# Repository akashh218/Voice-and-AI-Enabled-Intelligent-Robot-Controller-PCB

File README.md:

# Voice and AI-Enabled Intelligent Robot Controller PCB

A custom **4-layer embedded robotics controller PCB** designed for a multifunctional voice-interactive robot. The board integrates motor control, servo control, voice recognition, AI audio interaction, environmental monitoring, RGB indication, and dedicated interfaces into a compact custom-designed PCB.

## Features

* **ESP32-based main controller**
* **Dual DC motor control** using TB6612FNG
* **3 servo motor interfaces** for robotic movement and hand mechanisms
* **VC-02 AI Thinker voice recognition module** for offline voice commands
* **ICS-43434 digital microphone** for AI chatbot voice input
* **MAX98357A I2S audio amplifier** for audio output
* **Gemini AI chatbot interface** for online conversational interaction
* **WS2812 RGB LEDs** for status and visual indication
* **Temperature monitoring**
* **Automatic DC cooling fan control** based on temperature
* **Buzzer** for temperature and alert indication
* **USB-C programming interface** using CH340C
* Dedicated motor, servo, and system power distribution

## PCB Design

The PCB uses a **4-layer stackup**:

| Layer | Function            |
| ----- | ------------------- |
| L1    | Signal + Components |
| L2    | Solid GND Plane     |
| L3    | Power Distribution  |
| L4    | Signal              |

The multilayer design provides improved grounding, power distribution, signal integrity, and routing flexibility for the mixed-signal robotics system.

## Main Components

* ESP32 Controller Module
* TB6612FNG Motor Driver
* VC-02 AI Thinker Voice Recognition Module
* ICS-43434 MEMS Microphone
* MAX98357A I2S Audio Amplifier
* CH340C USB-to-UART
* WS2812 RGB LEDs
* Temperature Sensor
* DC Cooling Fan
* Buzzer
* Servo and DC Motor Connectors
* USB Type-C Connector
* Power Regulation and Filtering Components

## Applications

The controller is designed for:

* Voice-controlled robotics
* AI-assisted human-machine interaction
* Educational robotics
* Embedded AI systems
* Interactive robotic platforms
* Custom robotic control systems

## Design Tools

* **KiCad**
* Schematic Capture
* PCB Layout
* 4-Layer PCB Routing
* Design Rule Checking (DRC)
* 3D PCB Visualization

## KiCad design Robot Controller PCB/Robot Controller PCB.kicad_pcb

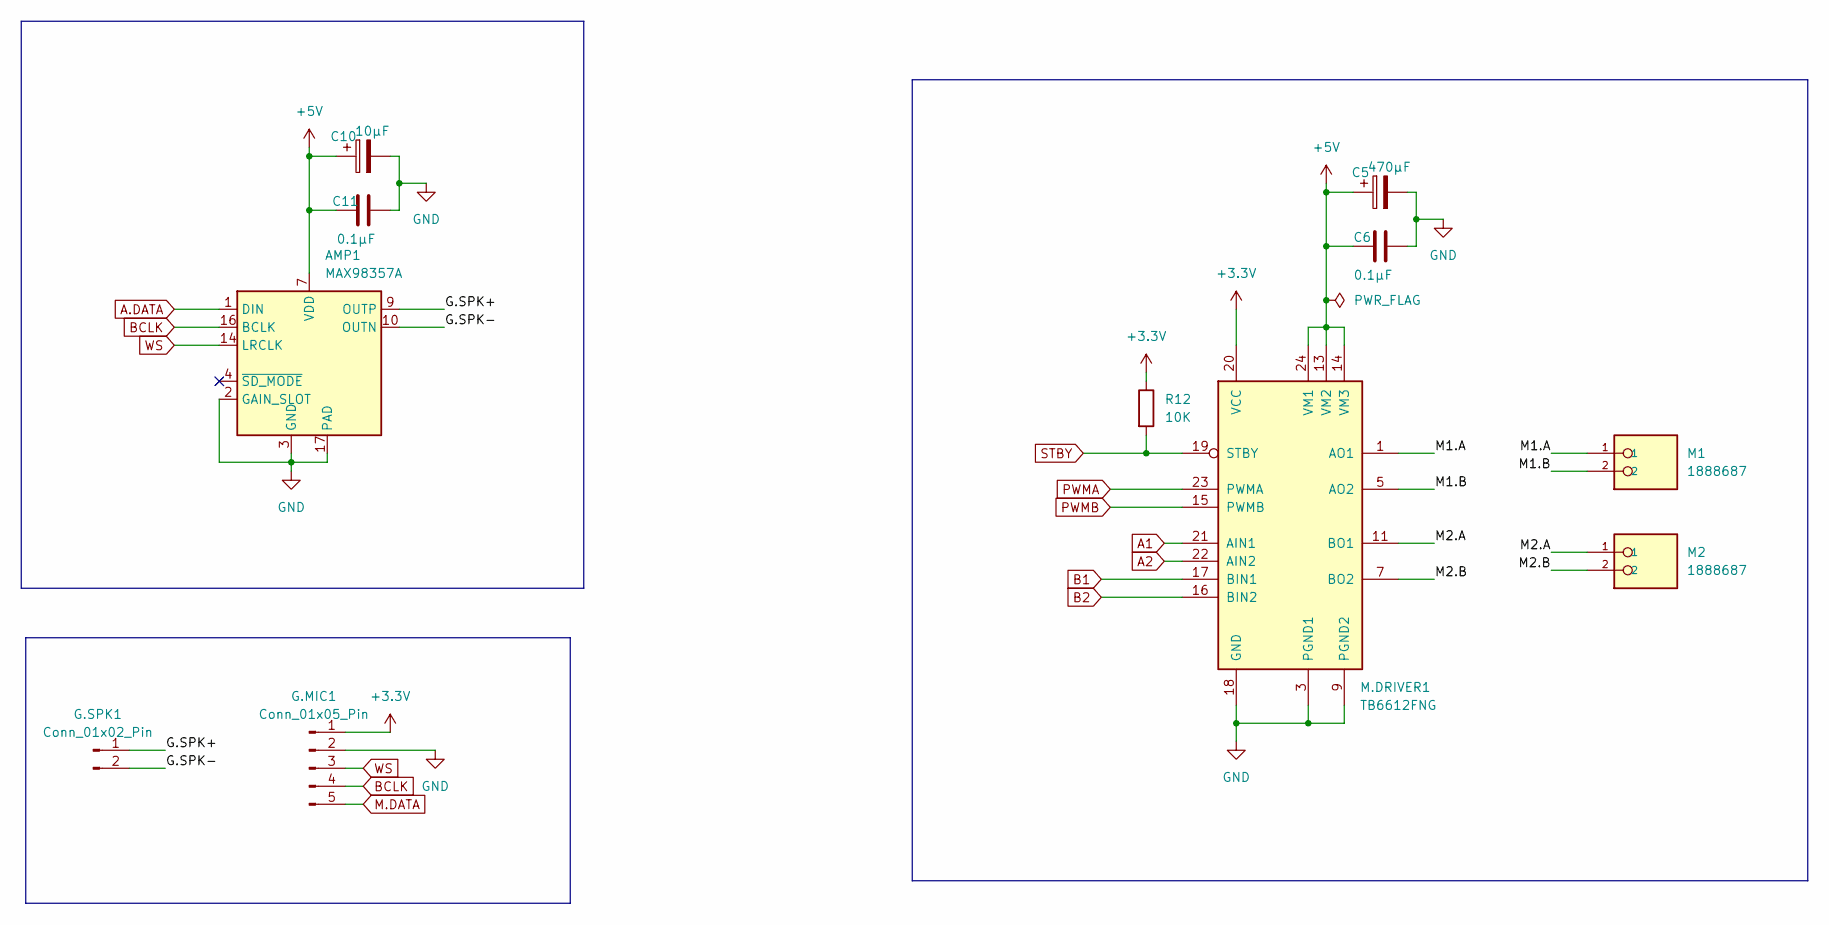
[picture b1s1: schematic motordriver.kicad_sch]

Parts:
AMP1: MAX98357A; TQFN-16-1EP_3x3mm_P0.5mm_EP1.23x1.23mm
C5: 470μF; CP_Elec_6.3x5.4
C6, C11: 0.1μF; C_0603_1608Metric
C10: 10μF; C_0805_2012Metric
G.MIC1: Conn_01x05_Pin; JST_PH_B5B-PH-K_1x05_P2.00mm_Vertical
G.SPK1: Conn_01x02_Pin; JST_PH_B2B-PH-K_1x02_P2.00mm_Vertical
M1, M2: 1888687; AMASS_XT30U-M_1x02_P5.0mm_Vertical; PARTREV 26.09.2015
M.DRIVER1: TB6612FNG; SSOP-24_5.3x8.2mm_P0.65mm
R12: 10K; R_0805_2012Metric

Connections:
+3.3V: G.MIC1.1, M.DRIVER1.20 (VCC), R12.1; also elsewhere on the board
+5V: AMP1.7 (VDD), AMP1.8 (VDD), C5.1, C6.2, C10.1, C11.2, M.DRIVER1.13 (VM2), M.DRIVER1.14 (VM3), M.DRIVER1.24 (VM1); also elsewhere on the board
/motordriver+amplifier/G.SPK+: AMP1.9 (OUTP), G.SPK1.1
/motordriver+amplifier/G.SPK-: AMP1.10 (OUTN), G.SPK1.2
/motordriver+amplifier/M1.A: M1.1, M.DRIVER1.1 (AO1), M.DRIVER1.2 (AO1)
/motordriver+amplifier/M1.B: M1.2, M.DRIVER1.5 (AO2), M.DRIVER1.6 (AO2)
/motordriver+amplifier/M2.A: M2.1, M.DRIVER1.11 (BO1), M.DRIVER1.12 (BO1)
/motordriver+amplifier/M2.B: M2.2, M.DRIVER1.7 (BO2), M.DRIVER1.8 (BO2)
A1: M.DRIVER1.21 (AIN1); also elsewhere on the board
A2: M.DRIVER1.22 (AIN2); also elsewhere on the board
A.DATA: AMP1.1 (DIN); also elsewhere on the board
B1: M.DRIVER1.17 (BIN1); also elsewhere on the board
B2: M.DRIVER1.16 (BIN2); also elsewhere on the board
BCLK: AMP1.16 (BCLK), G.MIC1.4; also elsewhere on the board
GND: AMP1.2 (GAIN_SLOT), AMP1.3 (GND), AMP1.11 (GND), AMP1.15 (GND), AMP1.17 (PAD), C5.2, C6.1, C10.2, C11.1, G.MIC1.2, M.DRIVER1.3 (PGND1), M.DRIVER1.4 (PGND1), M.DRIVER1.9 (PGND2), M.DRIVER1.10 (PGND2), M.DRIVER1.18 (GND); also elsewhere on the board
M.DATA: G.MIC1.5; also elsewhere on the board
PWMA: M.DRIVER1.23 (PWMA); also elsewhere on the board
PWMB: M.DRIVER1.15 (PWMB); also elsewhere on the board
STBY: M.DRIVER1.19 (STBY), R12.2; also elsewhere on the board
WS: AMP1.14 (LRCLK), G.MIC1.3; also elsewhere on the board

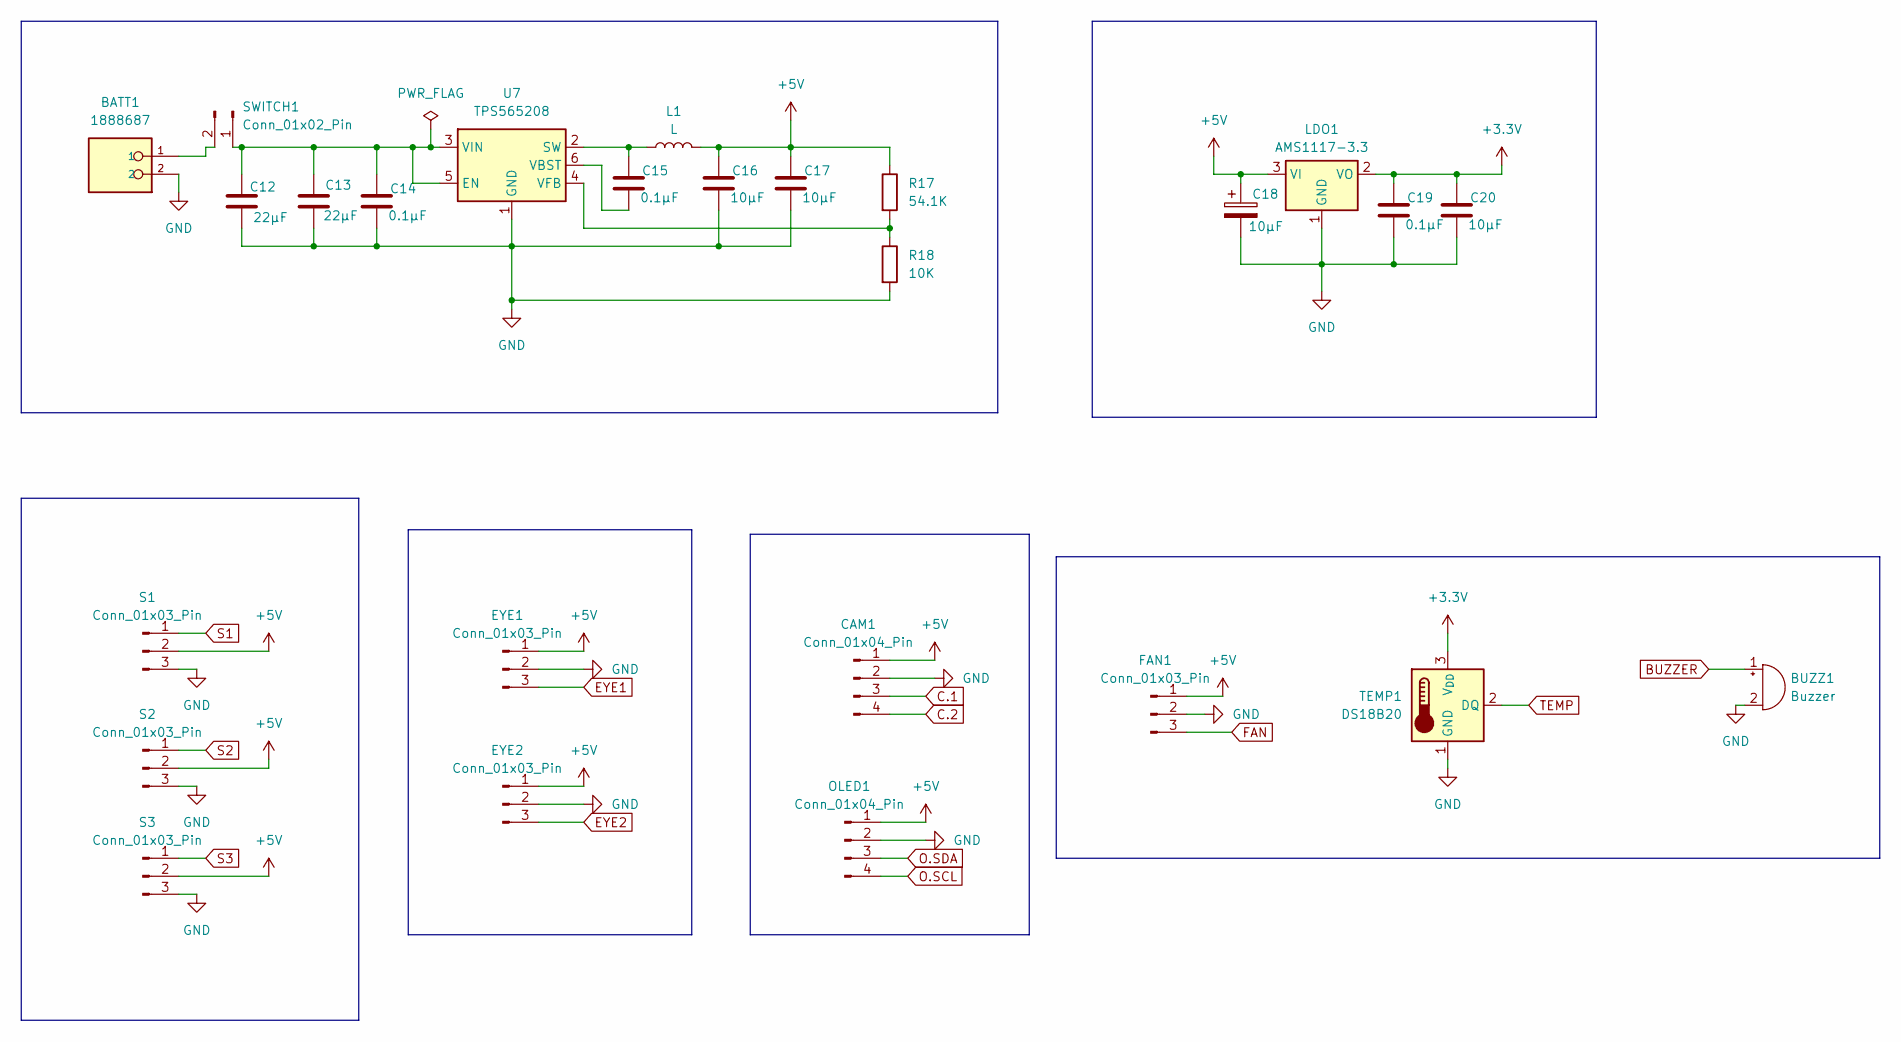
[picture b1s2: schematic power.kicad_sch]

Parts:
BATT1: 1888687; AMASS_XT30U-M_1x02_P5.0mm_Vertical; PARTREV 26.09.2015
BUZZ1: Buzzer; Buzzer_12x9.5RM7.6
C12, C13: 22μF; C_1206_3216Metric
C14, C15, C19: 0.1μF; C_0603_1608Metric
C16, C17, C18, C20: 10μF; C_0805_2012Metric
CAM1: Conn_01x04_Pin; JST_PH_B4B-PH-K_1x04_P2.00mm_Vertical
EYE1, EYE2: Conn_01x03_Pin; JST_PH_B3B-PH-K_1x03_P2.00mm_Vertical
FAN1: Conn_01x03_Pin; JST_PH_B3B-PH-K_1x03_P2.00mm_Vertical
L1: L; IND_VLCF5020T-3R3N2R0-1
LDO1: AMS1117-3.3; SOT-223-3_TabPin2
OLED1: Conn_01x04_Pin; JST_PH_B4B-PH-K_1x04_P2.00mm_Vertical
R17: 54.1K; R_0805_2012Metric
R18: 10K; R_0805_2012Metric
S1, S2, S3: Conn_01x03_Pin; JST_PH_B3B-PH-K_1x03_P2.00mm_Vertical
SWITCH1: Conn_01x02_Pin; JST_PH_B2B-PH-K_1x02_P2.00mm_Vertical
TEMP1: DS18B20; TO-92_Inline
U7: TPS565208; SOT-23-6

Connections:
+3.3V: C19.1, C20.1, LDO1.2 (VO), TEMP1.3 (V_{DD}); also elsewhere on the board
+5V: C16.1, C17.1, C18.1, CAM1.1, EYE1.1, EYE2.1, FAN1.1, L1.2, LDO1.3 (VI), OLED1.1, R17.1, S1.2, S2.2, S3.2; also elsewhere on the board
BUZZER: BUZZ1.1 (+); also elsewhere on the board
C.1: CAM1.3; also elsewhere on the board
C.2: CAM1.4; also elsewhere on the board
EYE1: EYE1.3; also elsewhere on the board
EYE2: EYE2.3; also elsewhere on the board
FAN: FAN1.3; also elsewhere on the board
GND: BATT1.2, BUZZ1.2 (-), C12.2, C13.2, C14.2, C16.2, C17.2, C18.2, C19.2, C20.2, CAM1.2, EYE1.2, EYE2.2, FAN1.2, LDO1.1 (GND), OLED1.2, R18.2, S1.3, S2.3, S3.3, TEMP1.1 (GND), U7.1 (GND); also elsewhere on the board
unnamed: C12.1, C13.1, C14.1, SWITCH1.1, U7.3 (VIN), U7.5 (EN)
unnamed: BATT1.1, SWITCH1.2
unnamed: C15.1, L1.1, U7.2 (SW)
unnamed: C15.2, U7.6 (VBST)
unnamed: R17.2, R18.1, U7.4 (VFB)
O.SCL: OLED1.4; also elsewhere on the board
O.SDA: OLED1.3; also elsewhere on the board
S1: S1.1; also elsewhere on the board
S2: S2.1; also elsewhere on the board
S3: S3.1; also elsewhere on the board
TEMP: TEMP1.2 (DQ); also elsewhere on the board

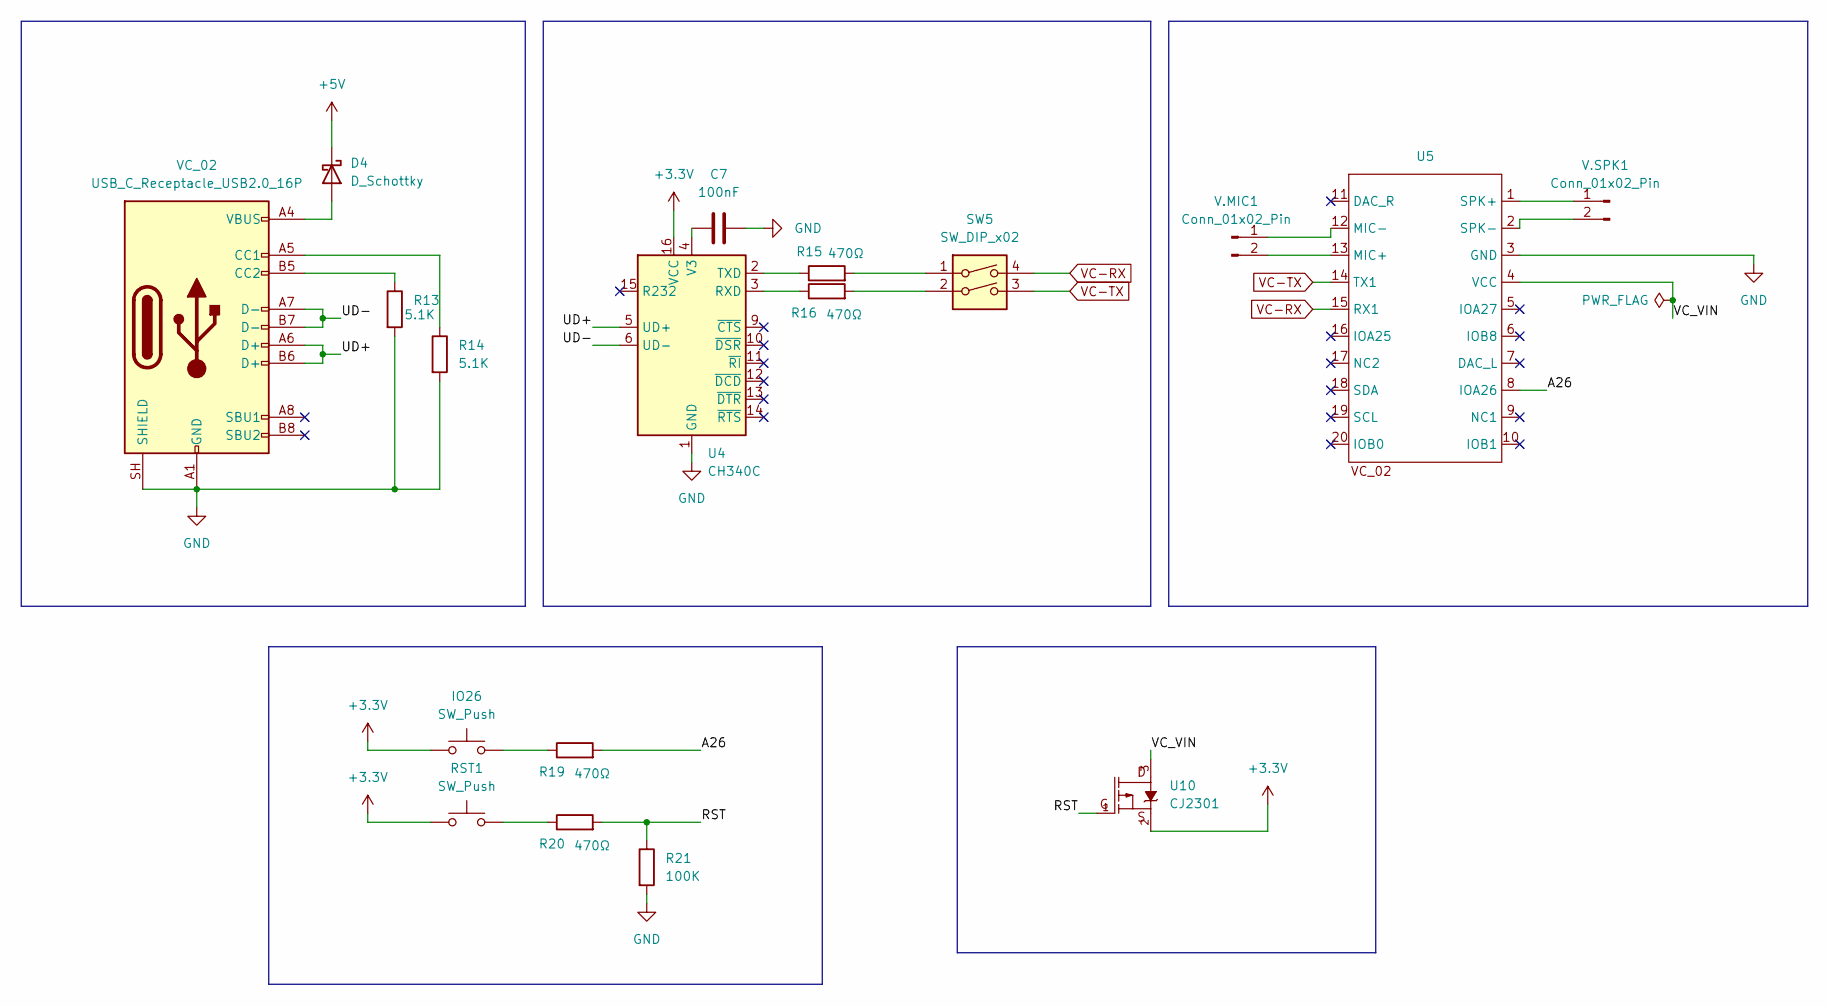
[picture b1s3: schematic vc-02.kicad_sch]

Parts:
C7: 100nF; CP_Elec_6.3x5.4
D4: D_Schottky; D_SMA
IO26: SW_Push; SW_Push_1P1T_NO_CK_KMR2
R13, R14: 5.1K; R_0805_2012Metric
R15, R16, R19, R20: 470Ω; R_0805_2012Metric
R21: 100K; R_0805_2012Metric
RST1: SW_Push; SW_Push_1P1T_NO_CK_KMR2
SW5: SW_DIP_x02; SW_DIP_SPSTx02_Slide_6.7x6.64mm_W6.73mm_P2.54mm_LowProfile_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
U4: CH340C; SOIC-16_3.9x9.9mm_P1.27mm
U5: Untitled
U10: CJ2301; SOT23-3
V.MIC1, V.SPK1: Conn_01x02_Pin; JST_PH_B2B-PH-K_1x02_P2.00mm_Vertical
VC_02: USB_C_Receptacle_USB2.0_16P; USB_C_Receptacle_HRO_TYPE-C-31-M-12

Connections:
+3.3V: IO26.1, RST1.1, U4.16 (VCC), U10.2; also elsewhere on the board
+5V: D4.1 (K); also elsewhere on the board
/vc-02/A26: R19.2, U5.8 (IOA26)
/vc-02/RST: R20.2, R21.1, U10.1
/vc-02/UD+: U4.5 (UD+), VC_02.A6 (D+), VC_02.B6 (D+)
/vc-02/UD-: U4.6 (UD-), VC_02.A7 (D-), VC_02.B7 (D-)
/vc-02/VC_VIN: U5.4 (VCC), U10.3
GND: C7.2, R13.2, R14.2, R21.2, U4.1 (GND), U5.3 (GND), VC_02.A1 (GND), VC_02.A12 (GND), VC_02.B1 (GND), VC_02.B12 (GND), VC_02.SH (SHIELD); also elsewhere on the board
unnamed: D4.2 (A), VC_02.A4 (VBUS), VC_02.A9 (VBUS), VC_02.B4 (VBUS), VC_02.B9 (VBUS)
unnamed: IO26.2, R19.1
unnamed: R15.2, SW5.1
unnamed: R16.2, SW5.2
unnamed: R20.1, RST1.2
unnamed: R16.1, U4.3 (RXD)
unnamed: R15.1, U4.2 (TXD)
unnamed: C7.1, U4.4 (V3)
unnamed: U5.13 (MIC+), V.MIC1.2
unnamed: U5.12 (MIC-), V.MIC1.1
unnamed: U5.1 (SPK+), V.SPK1.1
unnamed: U5.2 (SPK-), V.SPK1.2
unnamed: R14.1, VC_02.A5 (CC1)
unnamed: R13.1, VC_02.B5 (CC2)
VC-RX: SW5.4, U5.15 (RX1); also elsewhere on the board
VC-TX: SW5.3, U5.14 (TX1); also elsewhere on the board

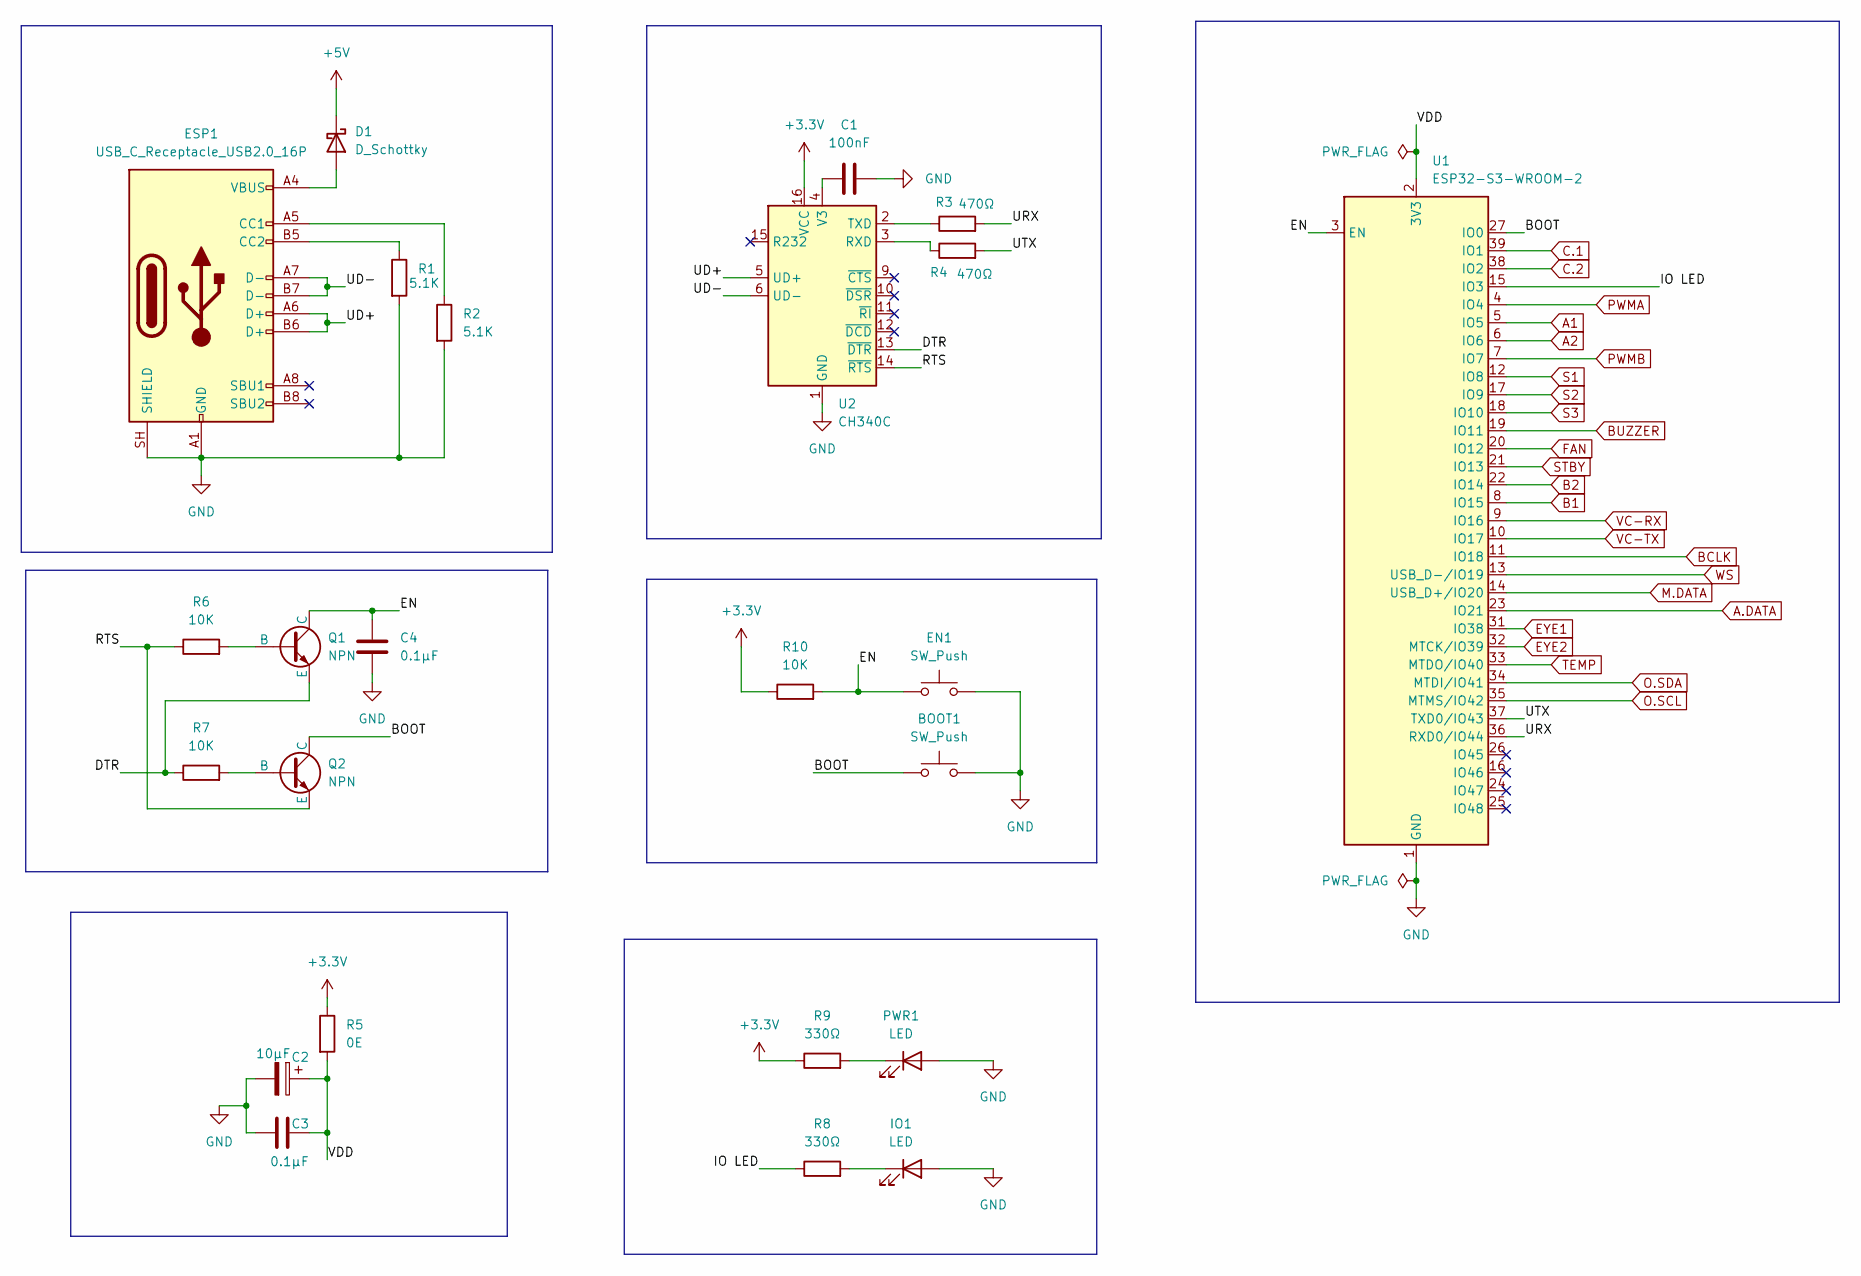
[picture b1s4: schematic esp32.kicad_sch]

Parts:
BOOT1: SW_Push; SW_Push_1P1T_NO_CK_KMR2
C1: 100nF; CP_Elec_6.3x5.4
C2: 10μF; C_0805_2012Metric
C3, C4: 0.1μF; C_0603_1608Metric
D1: D_Schottky; D_SMA
EN1: SW_Push; SW_Push_1P1T_NO_CK_KMR2
ESP1: USB_C_Receptacle_USB2.0_16P; USB_C_Receptacle_HRO_TYPE-C-31-M-12
IO1: LED; LED_0805_2012Metric_Pad1.15x1.40mm_HandSolder
PWR1: LED; LED_0805_2012Metric_Pad1.15x1.40mm_HandSolder
Q1, Q2: NPN; SOT-23
R1, R2: 5.1K; R_0805_2012Metric
R3, R4: 470Ω; R_0805_2012Metric
R5: 0E; R_0805_2012Metric
R6, R7, R10: 10K; R_0805_2012Metric
R8, R9: 330Ω; R_0805_2012Metric
U1: ESP32-S3-WROOM-2
U2: CH340C; SOIC-16_3.9x9.9mm_P1.27mm

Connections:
+3.3V: R5.1, R9.1, R10.1, U2.16 (VCC); also elsewhere on the board
+5V: D1.1 (K); also elsewhere on the board
/esp32/BOOT: BOOT1.1, Q2.1 (C), U1.27 (IO0); also elsewhere on the board
/esp32/DTR: Q1.3 (E), R7.1, U2.13 (~DTR)
/esp32/EN: C4.1, EN1.1, Q1.1 (C), R10.2, U1.3 (EN)
/esp32/IO LED: R8.1, U1.15 (IO3)
/esp32/RTS: Q2.3 (E), R6.1, U2.14 (~RTS)
/esp32/UD+: ESP1.A6 (D+), ESP1.B6 (D+), U2.5 (UD+)
/esp32/UD-: ESP1.A7 (D-), ESP1.B7 (D-), U2.6 (UD-)
/esp32/URX: R3.2, U1.36 (RXD0/IO44)
/esp32/UTX: R4.2, U1.37 (TXD0/IO43)
/esp32/VDD: C2.1, C3.2, R5.2, U1.2 (3V3)
A1: U1.5 (IO5); also elsewhere on the board
A2: U1.6 (IO6); also elsewhere on the board
A.DATA: U1.23 (IO21); also elsewhere on the board
B1: U1.8 (IO15); also elsewhere on the board
B2: U1.22 (IO14); also elsewhere on the board
BCLK: U1.11 (IO18); also elsewhere on the board
BUZZER: U1.19 (IO11); also elsewhere on the board
C.1: U1.39 (IO1); also elsewhere on the board
C.2: U1.38 (IO2); also elsewhere on the board
EYE1: U1.31 (IO38); also elsewhere on the board
EYE2: U1.32 (MTCK/IO39); also elsewhere on the board
FAN: U1.20 (IO12); also elsewhere on the board
GND: BOOT1.2, C1.2, C2.2, C3.1, C4.2, EN1.2, ESP1.A1 (GND), ESP1.A12 (GND), ESP1.B1 (GND), ESP1.B12 (GND), ESP1.SH (SHIELD), IO1.2 (A), PWR1.2 (A), R1.2, R2.2, U1.1 (GND), U1.40 (GND), U1.41 (GND), U2.1 (GND); also elsewhere on the board
M.DATA: U1.14 (USB_D+/IO20); also elsewhere on the board
unnamed: D1.2 (A), ESP1.A4 (VBUS), ESP1.A9 (VBUS), ESP1.B4 (VBUS), ESP1.B9 (VBUS)
unnamed: ESP1.A5 (CC1), R2.1
unnamed: ESP1.B5 (CC2), R1.1
unnamed: IO1.1 (K), R8.2
unnamed: PWR1.1 (K), R9.2
unnamed: Q1.2 (B), R6.2
unnamed: Q2.2 (B), R7.2
unnamed: R4.1, U2.3 (RXD)
unnamed: R3.1, U2.2 (TXD)
unnamed: C1.1, U2.4 (V3)
O.SCL: U1.35 (MTMS/IO42); also elsewhere on the board
O.SDA: U1.34 (MTDI/IO41); also elsewhere on the board
PWMA: U1.4 (IO4); also elsewhere on the board
PWMB: U1.7 (IO7); also elsewhere on the board
S1: U1.12 (IO8); also elsewhere on the board
S2: U1.17 (IO9); also elsewhere on the board
S3: U1.18 (IO10); also elsewhere on the board
STBY: U1.21 (IO13); also elsewhere on the board
TEMP: U1.33 (MTDO/IO40); also elsewhere on the board
VC-RX: U1.9 (IO16); also elsewhere on the board
VC-TX: U1.10 (IO17); also elsewhere on the board
WS: U1.13 (USB_D-/IO19); also elsewhere on the board

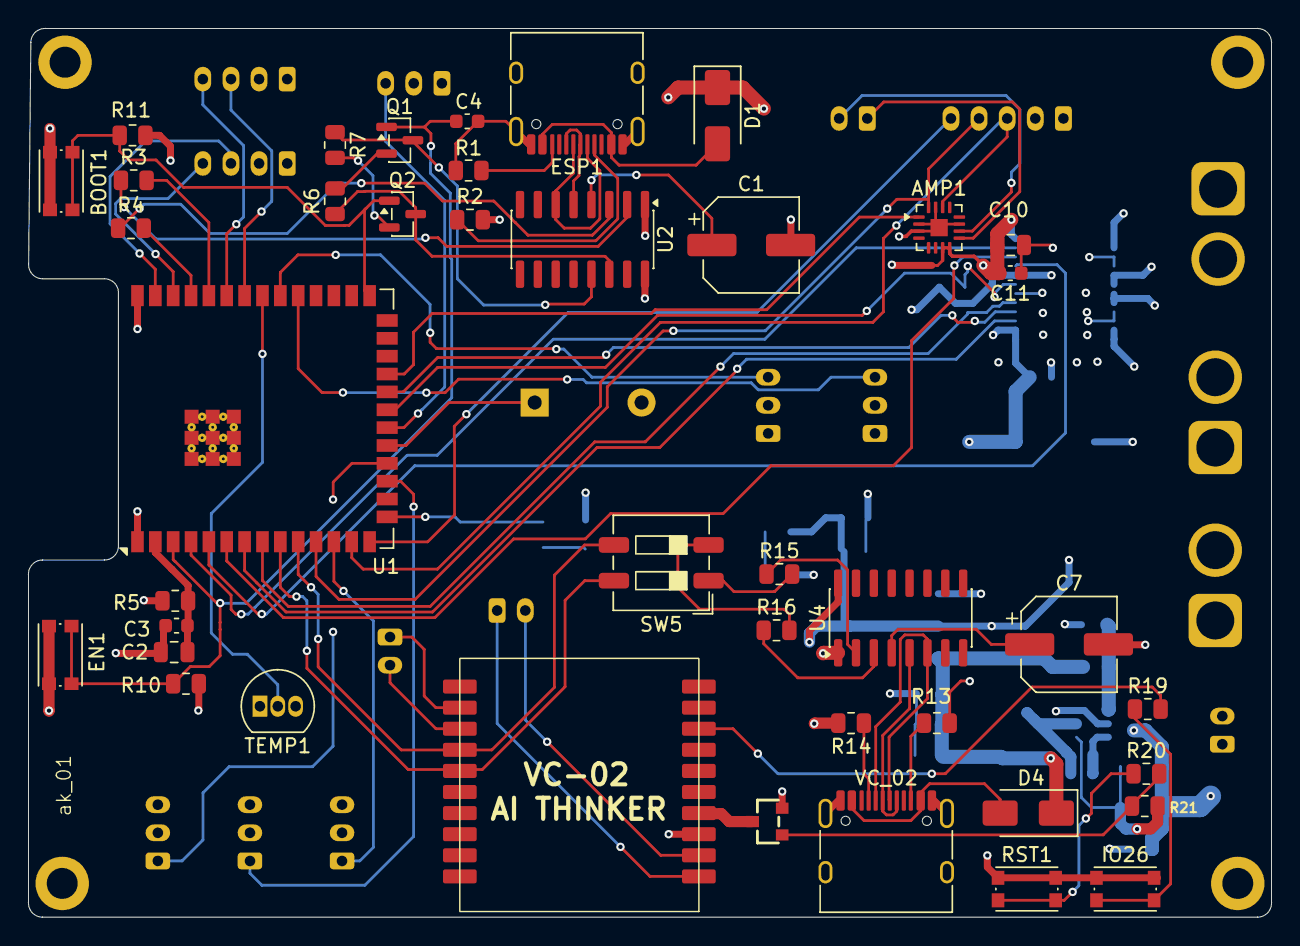
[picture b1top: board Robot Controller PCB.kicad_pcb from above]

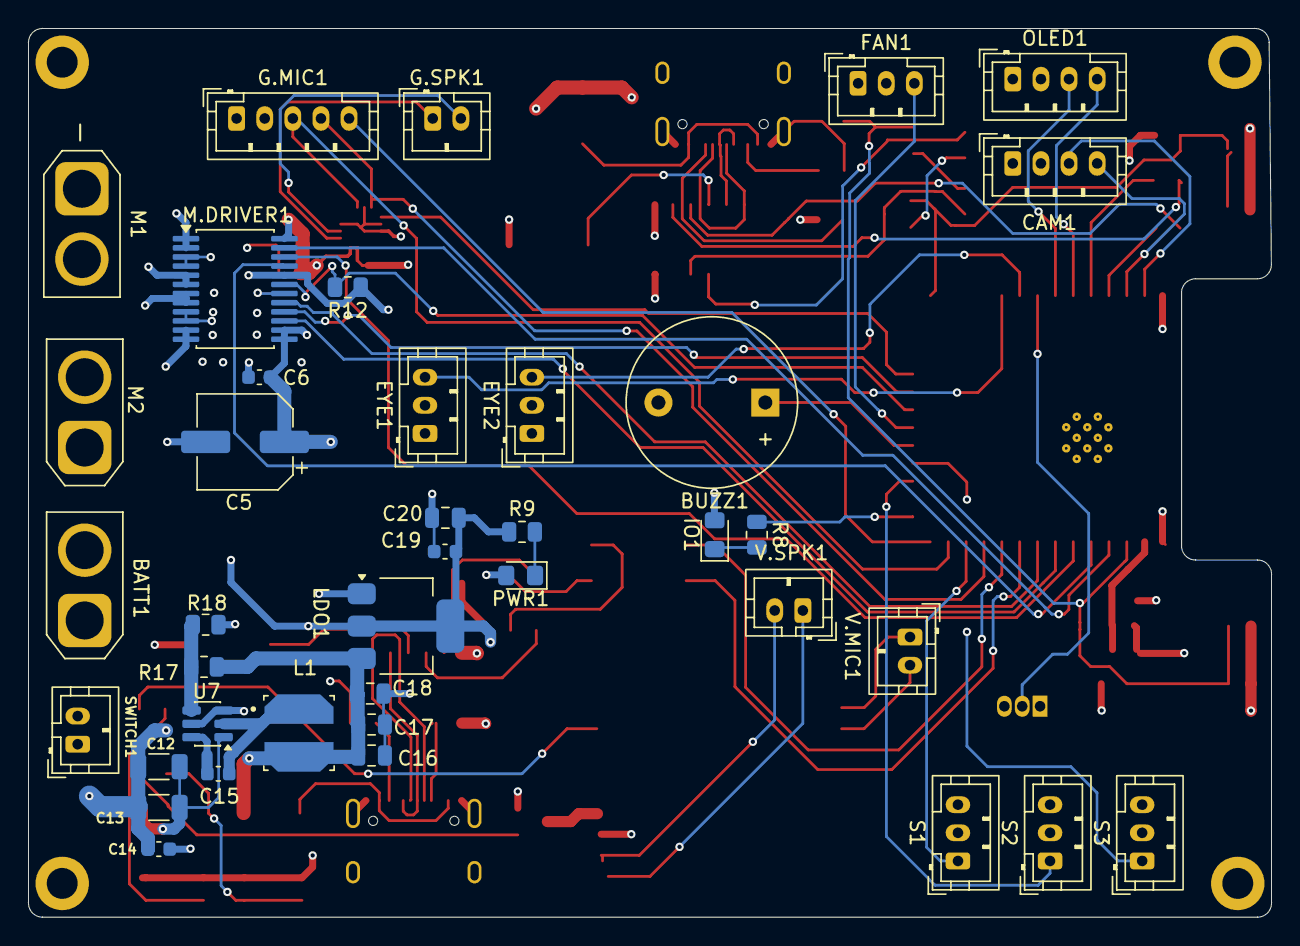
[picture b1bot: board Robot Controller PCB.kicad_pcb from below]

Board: 4 copper layers, 88.4 x 63.2 mm, 80 parts (39 on the bottom side), 78 nets.

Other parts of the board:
R11: 10K; R_0805_2012Metric

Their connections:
+3.3V: R11.1; also elsewhere on the board
/esp32/BOOT: R11.2; also elsewhere on the board
